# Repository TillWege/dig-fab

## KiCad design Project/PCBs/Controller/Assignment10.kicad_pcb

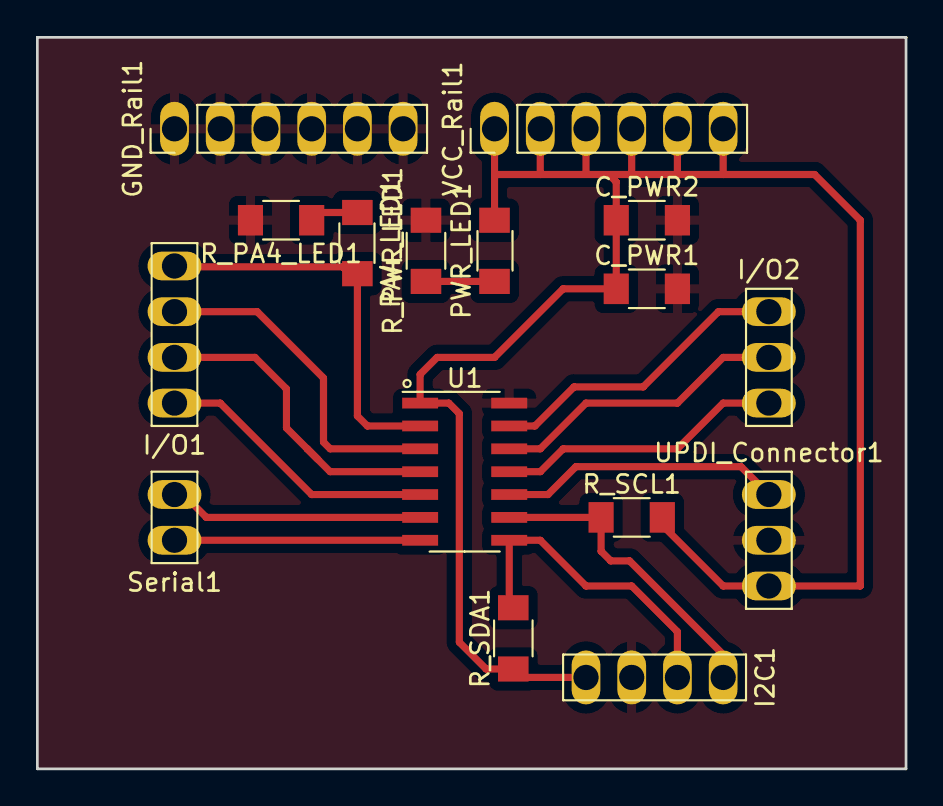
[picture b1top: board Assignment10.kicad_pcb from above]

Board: 2 copper layers, 48.3 x 40.6 mm, 16 parts (0 on the bottom side), 16 nets.

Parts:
C_PWR1: 1uf; C_1206
C_PWR2: 10uf; C_1206
GND_Rail1: Conn_PinHeader_1x06_P2.54mm_Vertical_THT_D1.4mm; PinHeader_1x06_P2.54mm_Vertical_THT_D1.4mm
I2C1: Conn_PinHeader_1x04_P2.54mm_Vertical_THT_D1.4mm; PinHeader_1x04_P2.54mm_Vertical_THT_D1.4mm
I/O1: Conn_PinHeader_1x04_P2.54mm_Vertical_THT_D1.4mm; PinHeader_1x04_P2.54mm_Vertical_THT_D1.4mm
I/O2: Conn_PinHeader_1x03_P2.54mm_Vertical_THT_D1.4mm; PinHeader_1x03_P2.54mm_Vertical_THT_D1.4mm
PA4_LED1: LED; LED_1206
PWR_LED1: LED; LED_1206
R_PA4_LED1: 499; R_1206
R_PWR_LED1: 499; R_1206
R_SCL1: 4.7k; R_1206
R_SDA1: 4.7k; R_1206
Serial1: Conn_PinHeader_1x02_P2.54mm_Vertical_THT_D1.4mm; PinHeader_1x02_P2.54mm_Vertical_THT_D1.4mm
U1: Microcontroller_ATtiny1614-SSFR; SOIC-14_3.9x8.7mm_P1.27mm
UPDI_Connector1: Conn_PinHeader_1x03_P2.54mm_Vertical_THT_D1.4mm; PinHeader_1x03_P2.54mm_Vertical_THT_D1.4mm
VCC_Rail1: Conn_PinHeader_1x06_P2.54mm_Vertical_THT_D1.4mm; PinHeader_1x06_P2.54mm_Vertical_THT_D1.4mm

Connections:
GND: C_PWR1.2, C_PWR2.2, GND_Rail1.1, GND_Rail1.2, GND_Rail1.3, GND_Rail1.4, GND_Rail1.5, GND_Rail1.6, I2C1.3, R_PA4_LED1.2, R_PWR_LED1.2, U1.14 (GND), UPDI_Connector1.2
unnamed: I/O1.1, U1.5 (PA7)
unnamed: I/O1.2, U1.4 (PA6/DAC)
unnamed: I/O1.3, U1.3 (PA5)
unnamed: I/O2.1, U1.13 (PA3/SCK)
unnamed: I/O2.2, U1.12 (PA2)
unnamed: I/O2.3, U1.11 (PA1)
unnamed: PA4_LED1.1 (K), R_PA4_LED1.1
unnamed: PWR_LED1.1 (K), R_PWR_LED1.1
PA4: I/O1.4, PA4_LED1.2 (A), U1.2 (PA4)
RXD: Serial1.2, U1.6 (PB3/RXD)
SCL: I2C1.1, R_SCL1.1, U1.9 (PB0/SCL)
SDA: I2C1.2, R_SDA1.2, U1.8 (PB1/SDA)
TXD: Serial1.1, U1.7 (PB2/TXD)
UPDI: U1.10 (~RESET/UPDI/PA0), UPDI_Connector1.1
VCC: C_PWR1.1, C_PWR2.1, I2C1.4, PWR_LED1.2 (A), R_SCL1.2, R_SDA1.1, U1.1 (VCC), UPDI_Connector1.3, VCC_Rail1.1, VCC_Rail1.2, VCC_Rail1.3, VCC_Rail1.4, VCC_Rail1.5, VCC_Rail1.6

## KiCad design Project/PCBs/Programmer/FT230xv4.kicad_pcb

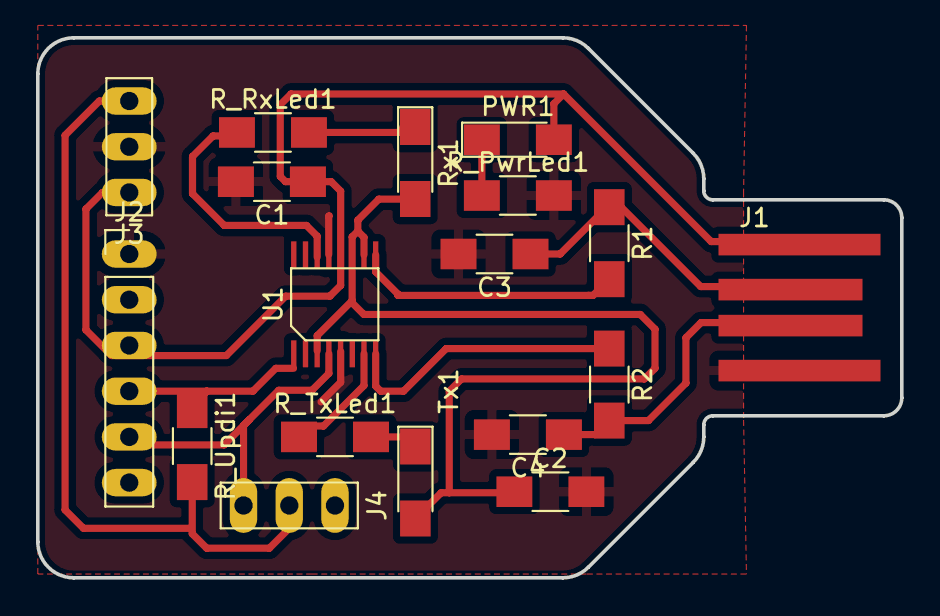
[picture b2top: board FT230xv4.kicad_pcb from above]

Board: 2 copper layers, 48.0 x 30.0 mm, 18 parts (0 on the bottom side), 15 nets.

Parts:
C1, C2: 1 uF; C_1206
C3, C4: 10 pF; C_1206
J1: USB_A_BoardPlug; Conn_USB_A_Plain
J2: Conn_01x06_Male; PinHeader_1x06_P2.54mm_Vertical_THT_D1.016mm
J3, J4: Conn_PinHeader_1x03_P2.54mm_Vertical_THT_D1.4mm; PinHeader_1x03_P2.54mm_Vertical_THT_D1mm
PWR1: LED; LED_1206
R1, R2: 49; R_1206
R_PwrLed1: 499; R_1206
R_RxLed1: 270; R_1206
R_TxLed1: 270; R_1206
R_Updi1: 4.7k; R_1206
Rx1: LED; LED_1206
Tx1: LED; LED_1206
U1: FT230XS; SSOP-16_3.9x4.9_P0.65mm

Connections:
+5V: C1.1, J1.1 (VBUS), J2.3, J3.1, PWR1.2 (A), U1.12 (VCC)
D+: R2.1, U1.8 (USBDP)
D-: R1.2, U1.9 (USBDM)
GND: C1.2, C2.2, C3.2, C4.2, J1.4 (GND), J2.1, J3.2, R_PwrLed1.2, U1.5 (GND), U1.13 (GND)
unnamed: C3.1, J1.2 (D-), R1.1
unnamed: C4.1, J1.3 (D+), R2.2
unnamed: J3.3, J4.2, R_Updi1.2
unnamed: PWR1.1 (K), R_PwrLed1.1
unnamed: R_RxLed1.2, Rx1.1 (K)
unnamed: R_TxLed1.2, Tx1.1 (K)
RX: J2.5, J4.3, U1.4 (RXD)
RxLed: R_RxLed1.1, U1.14 (CBUS1)
TX: J2.4, R_Updi1.1, U1.1 (TXD)
TxLed: R_TxLed1.1, U1.7 (CBUS2)
VCCIO: C2.1, Rx1.2 (A), Tx1.2 (A), U1.3 (VCCIO), U1.10 (3V3OUT), U1.11 (~RESET)

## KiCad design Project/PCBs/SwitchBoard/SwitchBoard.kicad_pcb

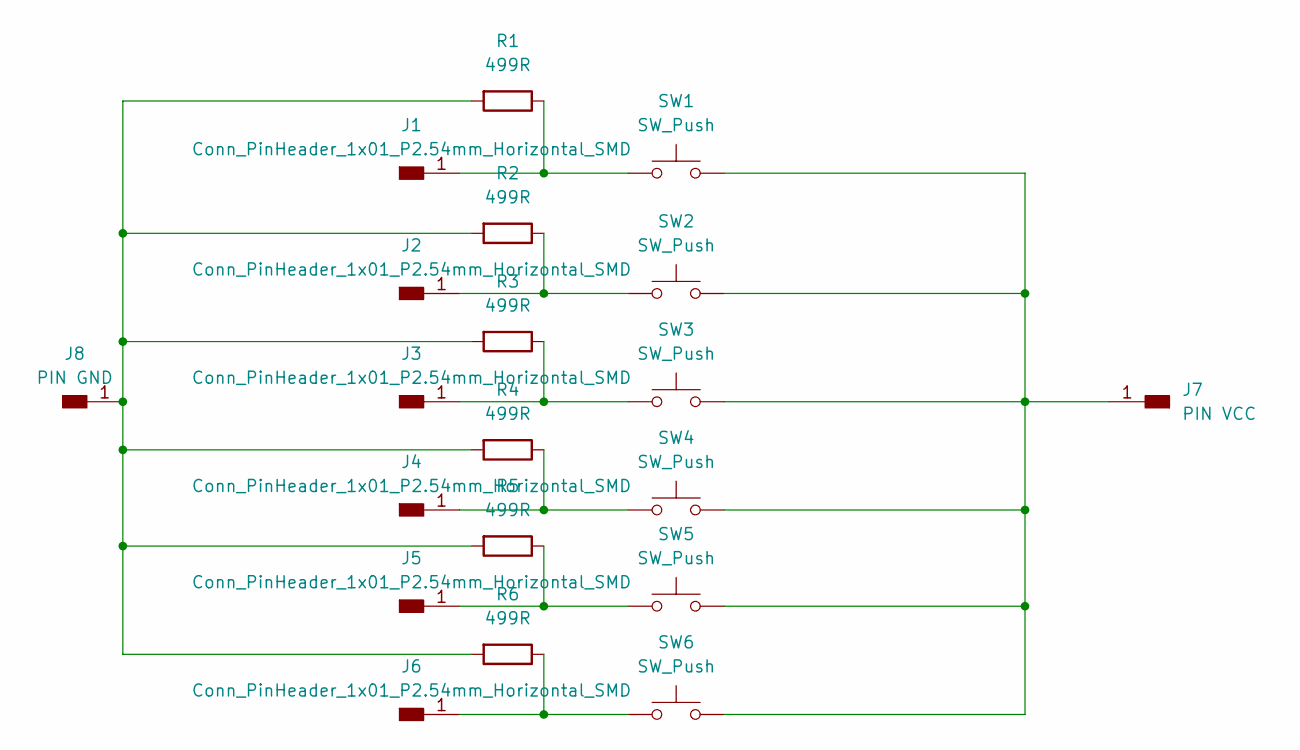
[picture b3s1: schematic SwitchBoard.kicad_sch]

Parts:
J1, J2, J3, J4, J5, J6: Conn_PinHeader_1x01_P2.54mm_Horizontal_SMD; PinHeader_1x01_P2.54mm_Vertical_THT_D1mm
J7: PIN VCC; PinHeader_1x02_P2.54mm_Vertical_THT_D1mm
J8: PIN GND; PinHeader_1x02_P2.54mm_Vertical_THT_D1mm
R1, R2, R3, R4, R5, R6: 499R; R_1206
SW1, SW2, SW3, SW4, SW5, SW6: SW_Push; SW_Cherry_MX_Plate

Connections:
unnamed: J1.1, R1.1, SW1.1
unnamed: J2.1, R2.1, SW2.1
unnamed: J3.1, R3.1, SW3.1
unnamed: J4.1, R4.1, SW4.1
unnamed: J5.1, R5.1, SW5.1
unnamed: J6.1, R6.1, SW6.1
unnamed: J7.1, SW1.2, SW2.2, SW3.2, SW4.2, SW5.2, SW6.2
unnamed: J8.1, R1.2, R2.2, R3.2, R4.2, R5.2, R6.2

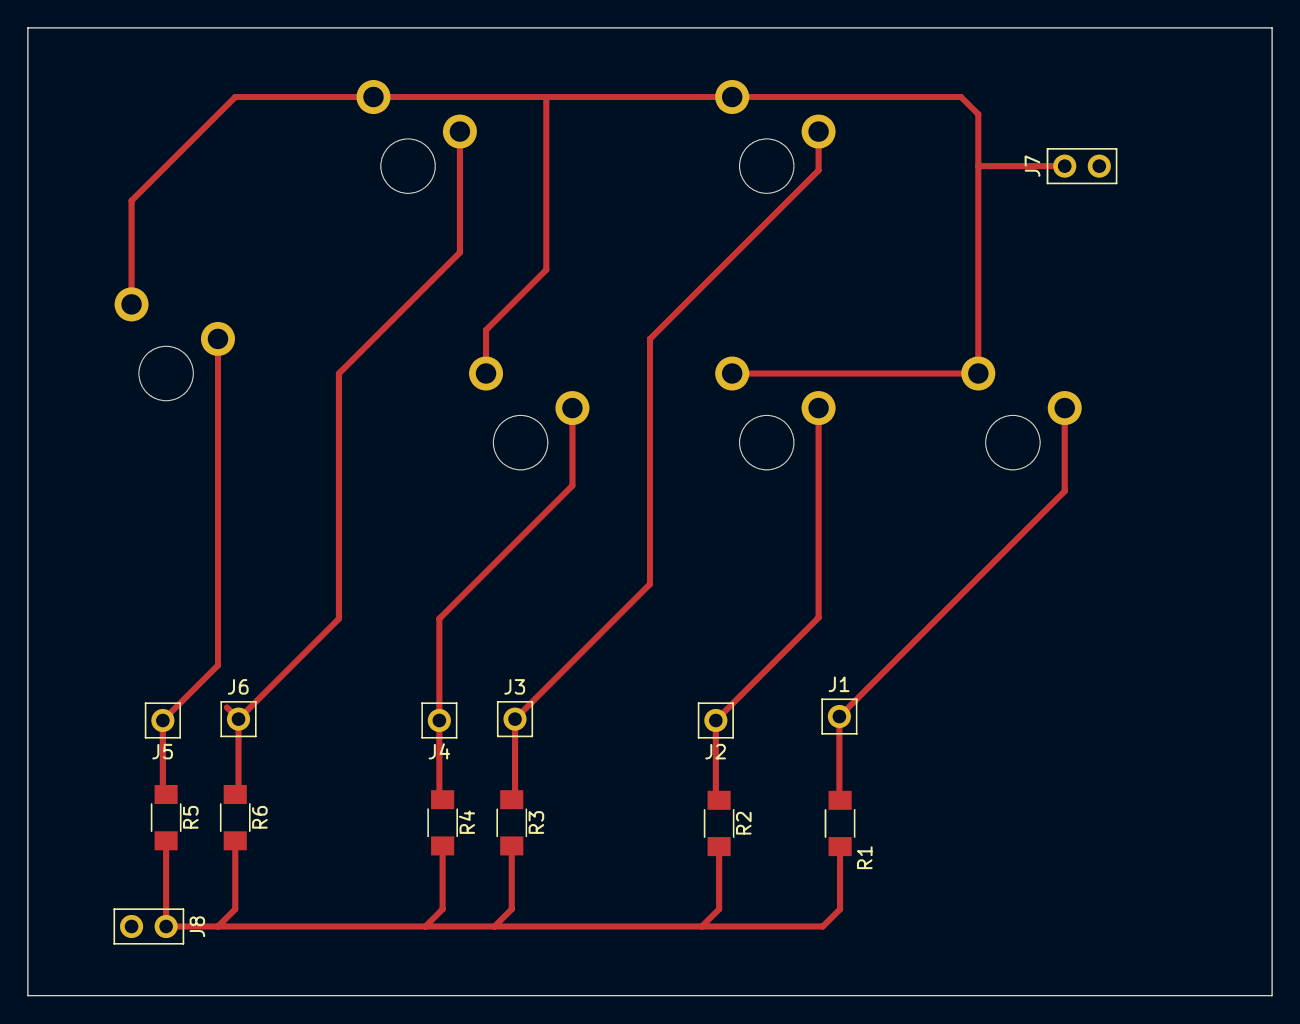
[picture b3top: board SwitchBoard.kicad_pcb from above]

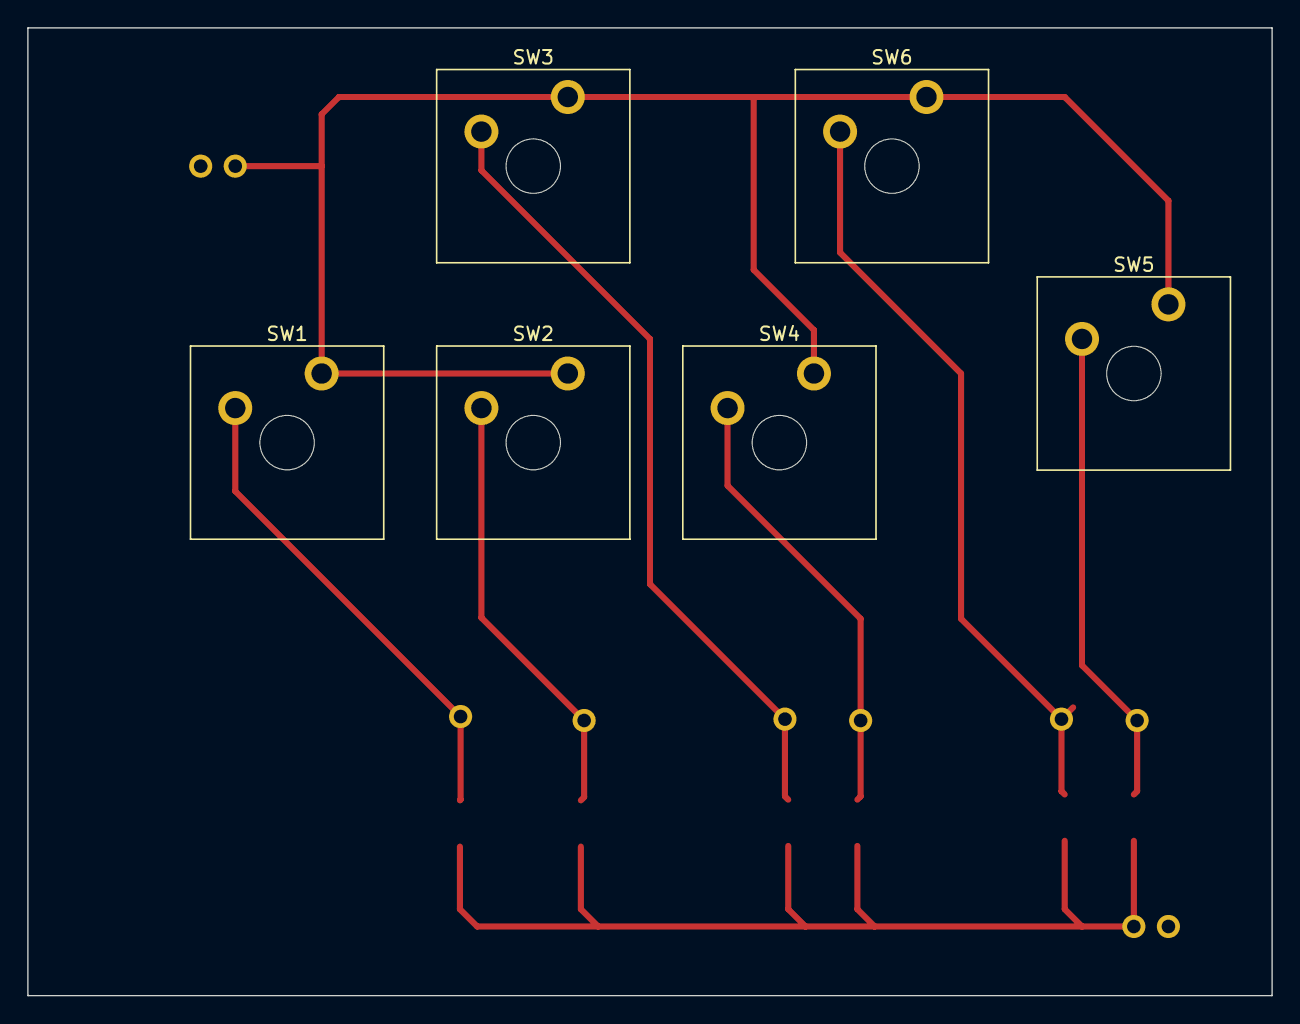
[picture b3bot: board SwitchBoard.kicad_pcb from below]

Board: 2 copper layers, 91.4 x 71.1 mm, 20 parts (6 on the bottom side), 8 nets.

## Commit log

2023-10-11 assignment 1
2023-10-11 assignment 1 images
2023-10-16 assignment 2
2023-10-24 fix structure
2023-11-06 df: add assignment 4
2023-11-13 Add Assignment 5
2023-11-20 Assignment 6: Simulation
2023-11-27 Assignment 7: I/O part 1
2024-02-10 Add PCB Designs
2024-02-10 fix paths for windows
2024-02-13 project case + initial code
2024-02-14 code v1
2024-02-18 add assignment 8 images
2024-02-18 Assignment 9 images
2024-02-20 project orga
2024-02-20 cleanup code
